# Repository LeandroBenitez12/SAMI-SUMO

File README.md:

# Robot Sumo Sami 🤖🏆

## Descripción del Proyecto

Este repositorio contiene el código y los recursos utilizados para el desarrollo de un robot Sumo llamado Sami.

El proyecto fue iniciado en 2022 por un grupo de estudiantes de Robótica del Industrial de Temperley, Buenos Aires, Argentina, entre ellos Leandro Benitez, Ezequiel Sierra, Abril Moyano y Facundo Timwki. Contamos con la invaluable colaboración de nuestro profesor, el Ingeniero Bustos Mariano.

Sami es un robot compacto y bien equilibrado diseñado específicamente para competir en las competencias de robótica, en particular en la Liga Nacional de Robótica (LNR) en Argentina. Durante el proceso de desarrollo, logramos el título de campeones en una competencia de robótica en el Instituto Técnico Nuestra Señora De Itatí, además avanzamos en cuanto a desarrollo personal y grupal, obtuvimos experiencia en la programación, diseño de PCB, 3D, el armado de robots, y fundiendo plomo, entre otras cosas...

## Características del Robot

- **Microcontrolador ESP32** para un rendimiento potente y una amplia capacidad de conectividad.
- **Pantalla OLED** para visualizar menús y estrategias en tiempo real.
- **Drivers Pololu 24v13** para el control preciso de motores y la maniobrabilidad del robot.
- **Sensores Sharp GP2Y0A60SZLF** para detectar obstáculos y oponentes.
- **Sensores de piso QRE1113 SMD y un LDR** utilizados en diversas estrategias de detección.
- Alimentación con **2 baterías LiPo en serie de 3 celdas**, logrando una tensión de 24V.
- Uso de un **convertidor Step-Down** para bajar la tensión y alimentar el microcontrolador.

## Estructura del Repositorio

- **/Software:** Contiene el código de programación en C++ para el robot Sami, basado en el entorno Arduino, y las librerías personalizadas.
- **/Hardware:** Incluye el diseño 3D del robot Sami, así como recursos relacionados con el armado físico y moldeado de plomo para alcanzar el límite de peso en la competencia.

## Instrucciones de Uso

1. Clona el repositorio en tu computadora local para acceder a todos los recursos y el código.
2. Explora el contenido de **/Software** para conocer la programación del robot y las diferentes estrategias disponibles.
3. Consulta el diseño 3D y la información en **/Hardware** para comprender la estructura y los componentes utilizados.

## Cómo Contribuir

¡Valoramos y agradecemos cualquier contribución que puedas brindar para mejorar nuestro robot Sami! Si deseas colaborar, sugerir mejoras o corregir problemas, sigue estos pasos:

1. Haz un fork de este repositorio y clona tu copia localmente.
2. Realiza los cambios y mejoras en tu rama, incluso si es para sugerir posibles soluciones o nuevas ideas.
3. Asegúrate de agregar o actualizar la documentación con tus contribuciones.
4. Realiza un pull request a nuestra rama principal para que podamos revisar y considerar tus aportes.

y videos....

https://github.com/LeandroBenitez12/SAMI_RBSUMO/assets/108737751/56b0725f-8328-4741-986b-e7431d0c3679

## Contacto

¡Nos encantaría recibir tus comentarios, sugerencias y cualquier tipo de feedback que nos ayude a mejorar nuestro proyecto Sami! Si deseas ponerte en contacto con nosotros, no dudes en escribirnos a:

- Leandro Benitez: leandrobenitezz2004@gmail.com
- Ezequiel Sierra: Sierraezequiel75@gmail.com

## Agradecimientos

Queremos expresar nuestro agradecimiento a todas las personas que nos han brindado apoyo y colaboración en este proyecto. ¡Sin su ayuda, no habríamos llegado tan lejos en el desarrollo de Sami y en nuestras competencias!

¡Estamos entusiasmados con los avances logrados hasta el momento y esperamos seguir mejorando y refinando nuestro robot Sumo Sami en el futuro! 🤖🏆

¡Gracias por tu interés en nuestro proyecto! Si necesitas más información o tienes otras preguntas, no dudes en hacérmelas. ¡Éxito en tus futuras competencias de robótica!

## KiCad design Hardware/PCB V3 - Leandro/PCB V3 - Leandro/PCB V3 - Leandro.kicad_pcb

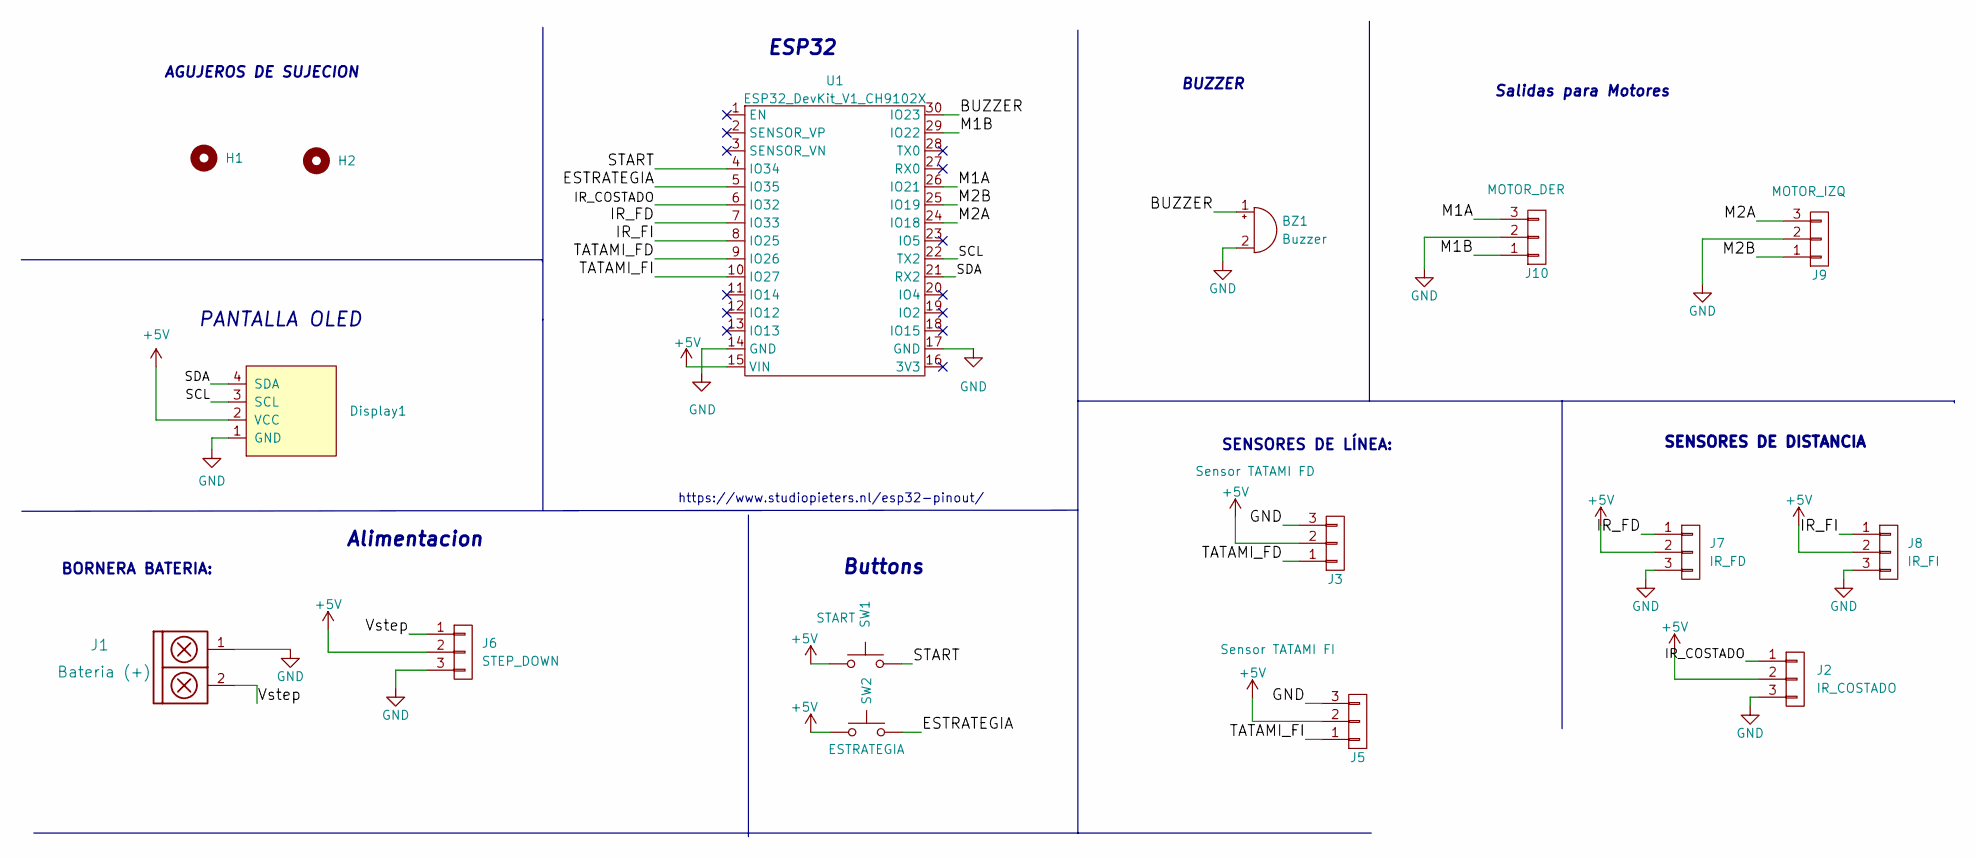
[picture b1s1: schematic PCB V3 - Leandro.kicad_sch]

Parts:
BZ1: Buzzer; Pin_strip_2
Display1: SSD1306-SSD1306-128x64_OLED; 128x64OLED
H1, H2: Mounting_Hole; pad_3mm
J1: Bateria (+); BORNERA2_AZUL
J2: IR_COSTADO; Pin_Strip_3
J3: Sensor TATAMI FD; Pin_Strip_3
J5: Sensor TATAMI FI; Pin_Strip_3
J6: STEP_DOWN; Pin_Strip_3
J7: IR_FD; Pin_Strip_3
J8: IR_FI; Pin_Strip_3
J9: MOTOR_IZQ; Pin_Strip_3
J10: MOTOR_DER; Pin_Strip_3
SW1: START; Pin_Header_2
SW2: ESTRATEGIA; Pin_Header_2
U1: ESP32_DevKit_V1_CH9102X

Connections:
+5V: Display1.2 (VCC), J2.2, J3.2, J5.2, J6.2, J7.2, J8.2, SW1.1, SW2.1, U1.15 (VIN)
/BUZZER: BZ1.1 (-), U1.30 (IO23)
/ESTRATEGIA: SW2.2, U1.5 (IO35)
/IR_COSTADO: J2.1, U1.6 (IO32)
/IR_FD: J7.1, U1.7 (IO33)
/IR_FI: J8.1, U1.8 (IO25)
/M1A: J10.3, U1.26 (IO21)
/M1B: J10.1, U1.29 (IO22)
/M2A: J9.3, U1.24 (IO18)
/M2B: J9.1, U1.25 (IO19)
/SCL: Display1.3 (SCL), U1.22 (TX2)
/SDA: Display1.4 (SDA), U1.21 (RX2)
/START: SW1.2, U1.4 (IO34)
/TATAMI_FD: J3.1, U1.9 (IO26)
/TATAMI_FI: J5.1, U1.10 (IO27)
/Vstep: J1.2, J6.1
GND: BZ1.2 (+), Display1.1 (GND), J1.1, J2.3, J3.3, J5.3, J6.3, J7.3, J8.3, J9.2, J10.2, U1.14 (GND), U1.17 (GND)

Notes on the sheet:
SENSORES DE LÍNEA:
Buttons
ESP32
BORNERA BATERIA:
https://www.studiopieters.nl/esp32-pinout/
PANTALLA OLED
Alimentacion
SENSORES DE DISTANCIA
AGUJEROS DE SUJECION
Salidas para Motores
BUZZER

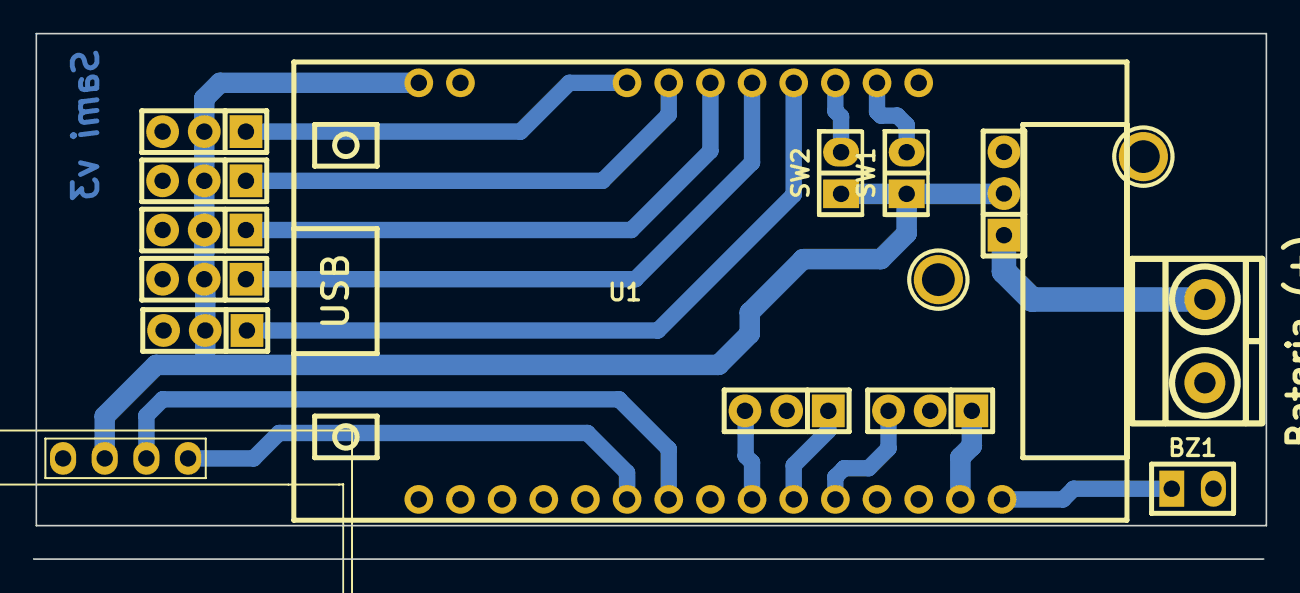
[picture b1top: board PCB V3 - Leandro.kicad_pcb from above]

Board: 2 copper layers, 75.2 x 32.0 mm, 16 parts (0 on the bottom side), 17 nets.

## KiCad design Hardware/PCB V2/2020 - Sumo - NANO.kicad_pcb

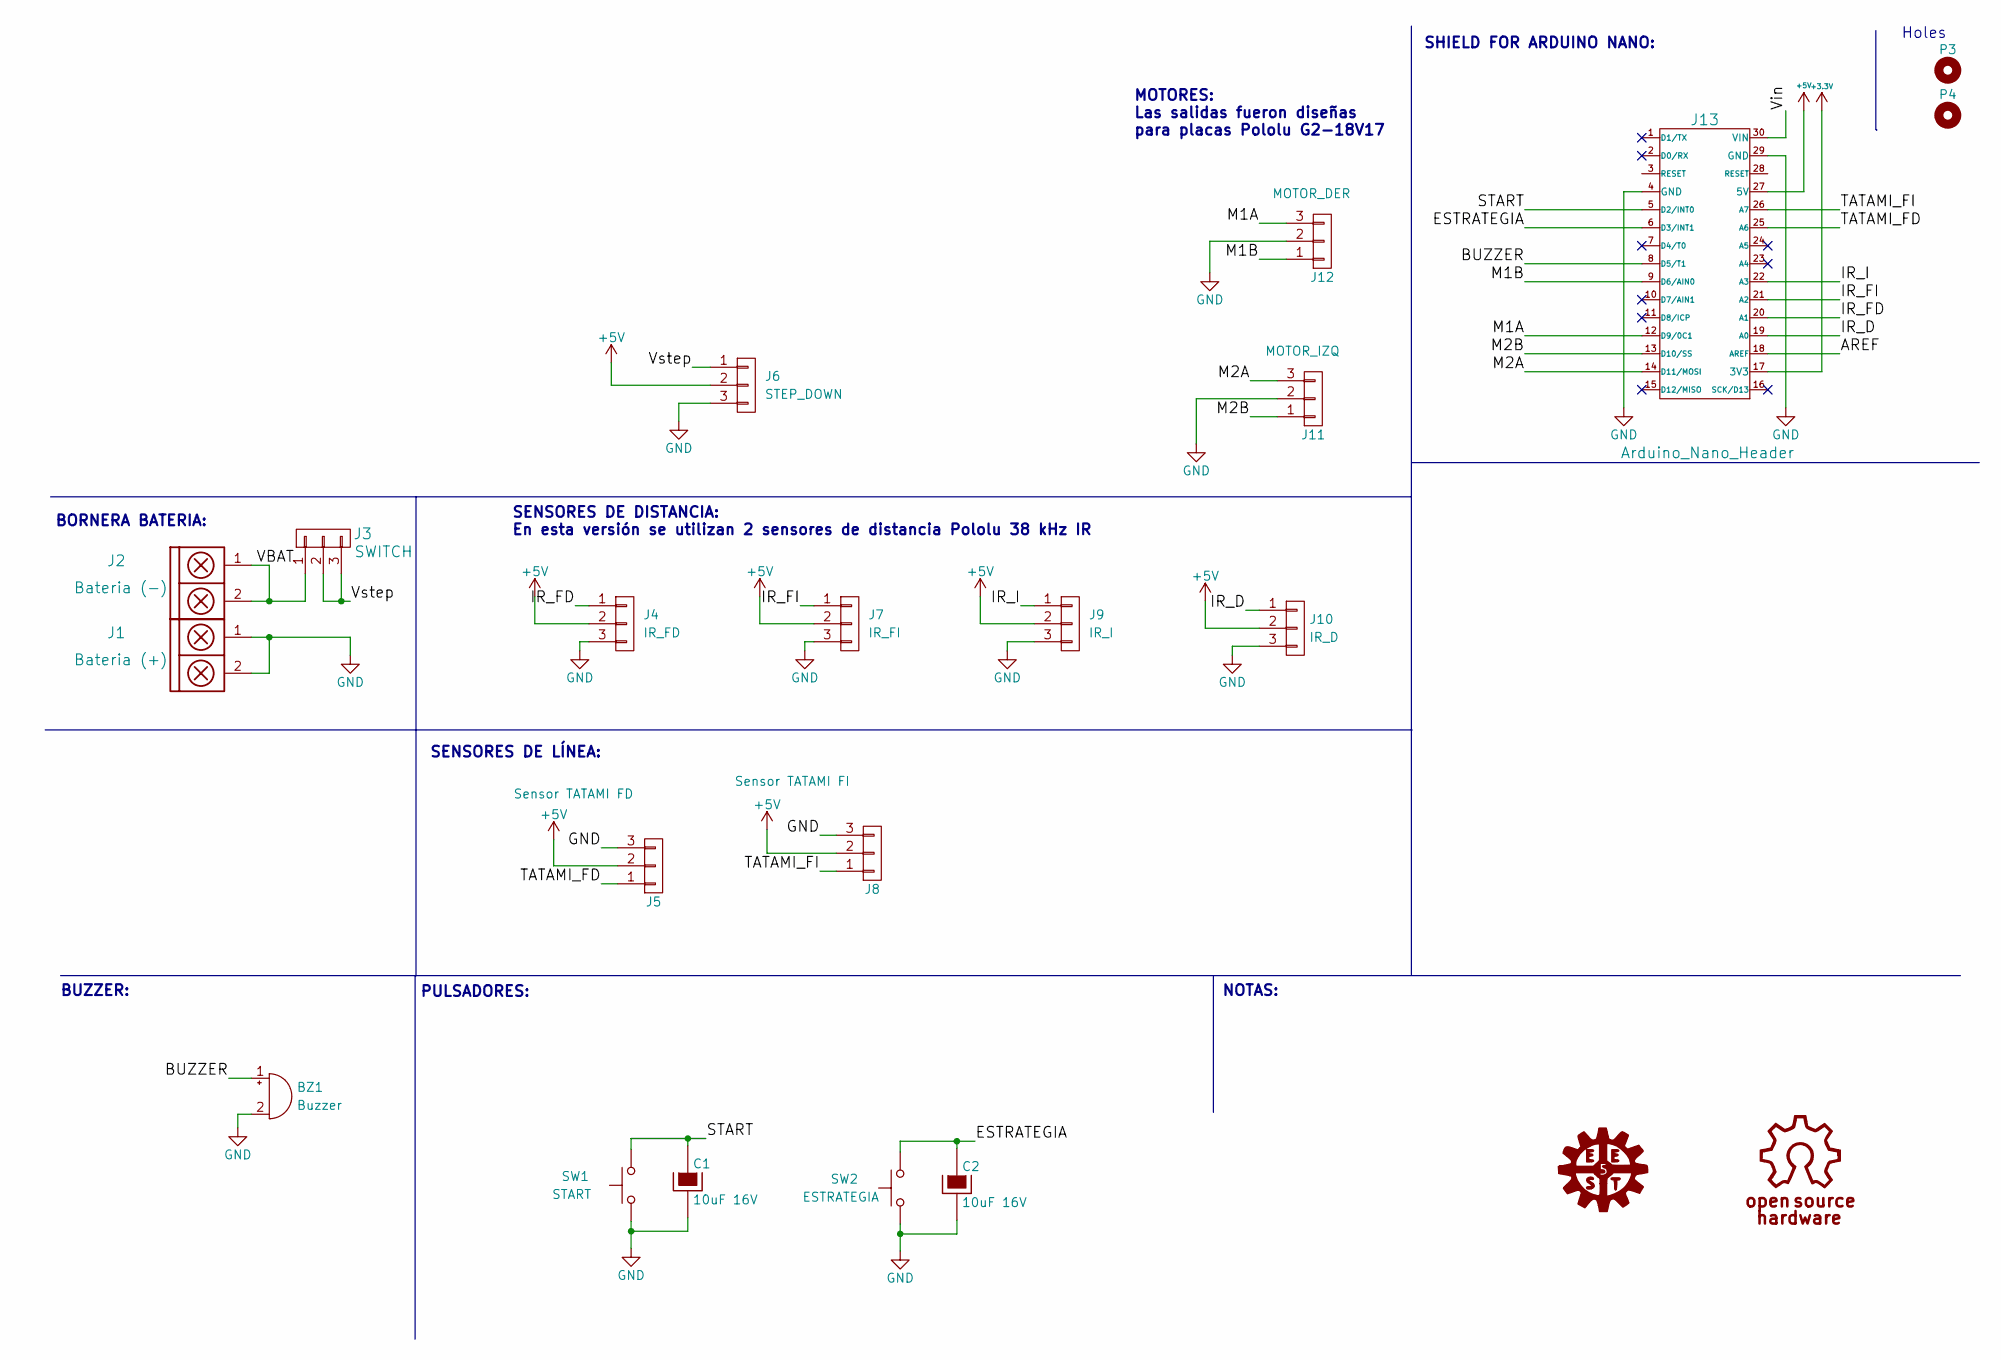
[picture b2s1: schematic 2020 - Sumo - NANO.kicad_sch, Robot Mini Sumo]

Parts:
BZ1: Buzzer; Pin_strip_2
C1, C2: 10uF 16V; CAP_TAN_A
J1: Bateria (+); BORNERA2_AZUL
J2: Bateria (-); BORNERA2_AZUL
J3: SWITCH; SW_SPDT_TH_Vertical
J4: IR_FD; Pin_Strip_3
J5: Sensor TATAMI FD; Pin_Strip_3
J6: STEP_DOWN; Pin_Strip_3
J7: IR_FI; Pin_Strip_3
J8: Sensor TATAMI FI; Pin_Strip_3
J9: IR_I; Pin_Strip_3
J10: IR_D; Pin_Strip_3
J11: MOTOR_IZQ; Pin_Strip_3
J12: MOTOR_DER; Pin_Strip_3
J13: Arduino_Nano_Header; arduino_nano_header
P3, P4: Mounting_Hole; Separador_M3_5mm
SW1: START; Pin_Header_2
SW2: ESTRATEGIA; Pin_Header_2

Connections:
+3V3: J13.17 (3V3)
+5V: J4.2, J5.2, J6.2, J7.2, J8.2, J9.2, J10.2, J13.27 (5V)
/AREF: J13.18 (AREF)
/BUZZER: BZ1.1 (-), J13.8 (D5/T1)
/ESTRATEGIA: C2.1, J13.6 (D3/INT1), SW2.2
/IR_D: J10.1, J13.19 (A0)
/IR_FD: J4.1, J13.20 (A1)
/IR_FI: J7.1, J13.21 (A2)
/IR_I: J9.1, J13.22 (A3)
/M1A: J12.3, J13.12 (D9/0C1)
/M1B: J12.1, J13.9 (D6/AIN0)
/M2A: J11.3, J13.14 (D11/MOSI)
/M2B: J11.1, J13.13 (D10/SS)
/START: C1.1, J13.5 (D2/INT0), SW1.2
/TATAMI_FD: J5.1, J13.25 (A6)
/TATAMI_FI: J8.1, J13.26 (A7)
/VBAT: J2.1, J2.2, J3.1
/Vin: J13.30 (VIN)
/Vstep: J3.2, J3.3, J6.1
GND: BZ1.2 (+), C1.2, C2.2, J1.1, J1.2, J4.3, J5.3, J6.3, J7.3, J8.3, J9.3, J10.3, J11.2, J12.2, J13.4 (GND), J13.29 (GND), SW1.1, SW2.1

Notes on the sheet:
SENSORES DE LÍNEA:
MOTORES: Las salidas fueron diseñas para placas Pololu G2-18V17
Holes
BORNERA BATERIA:
NOTAS:
BUZZER:
SHIELD FOR ARDUINO NANO:
SENSORES DE DISTANCIA: En esta versión se utilizan 2 sensores de distancia Pololu 38 kHz IR
PULSADORES:

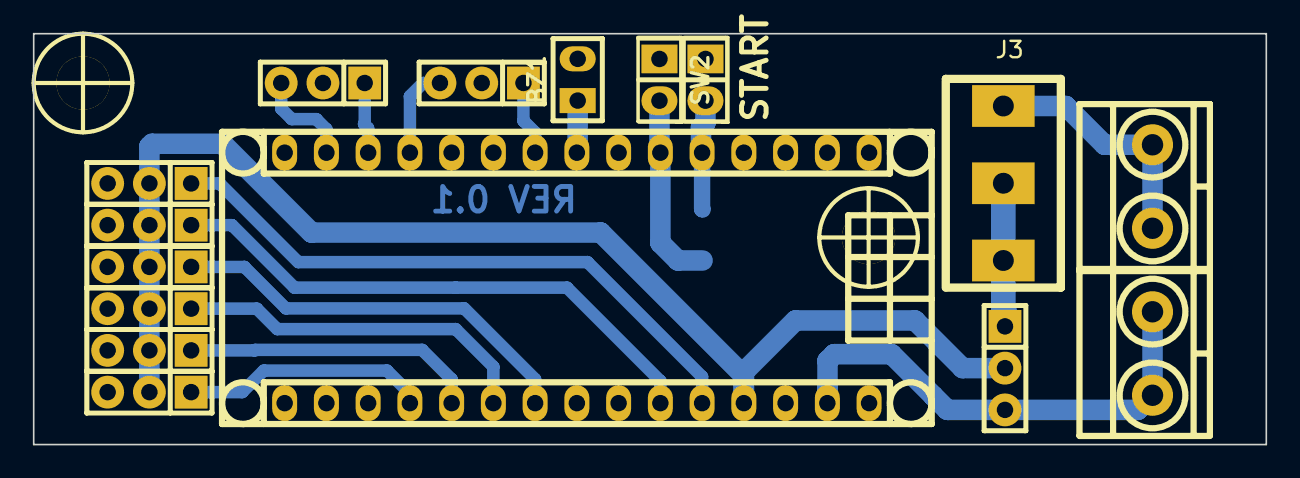
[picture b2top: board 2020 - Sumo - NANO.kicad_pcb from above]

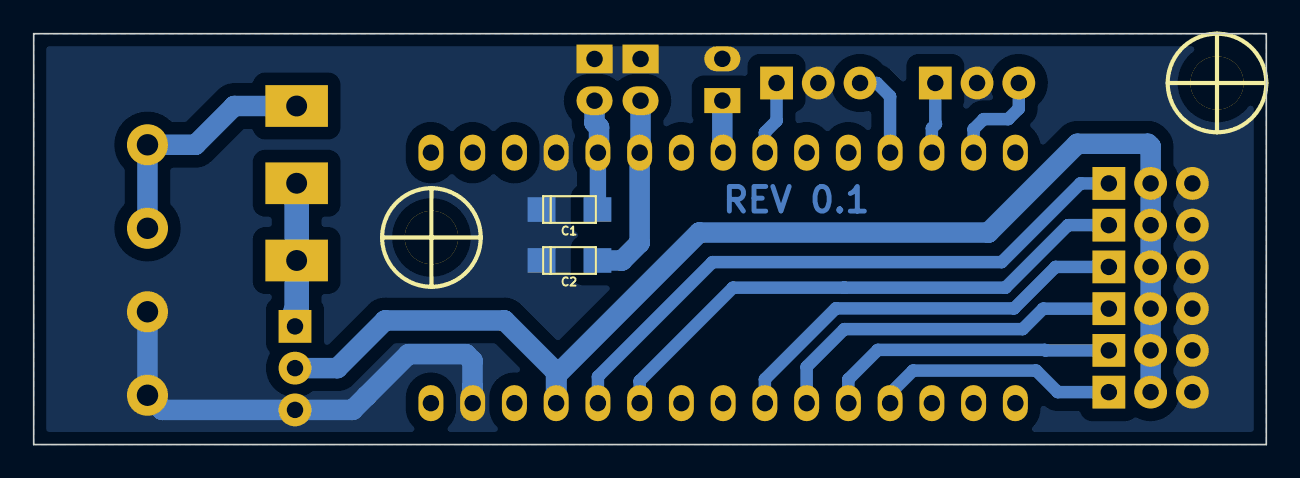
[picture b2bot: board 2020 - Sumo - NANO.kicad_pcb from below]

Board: 2 copper layers, 75.0 x 25.0 mm, 20 parts (2 on the bottom side), 17 nets.

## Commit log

2022-08-27 Add the folders
2022-08-27 el robot ahora detecta sensores de piso y gira
2022-08-27 Realice POO de motores
2022-08-27 Realice el POO de sensores anda bien
2022-08-27 Correciones sugeridas por angel y agregue class button y buzzer
2022-08-27 Realice la maquina de estados pero tengo problemas
2022-08-27 Ahora anda gracias f0n
2022-08-29 codigo inicial echo por Lenadro
2022-08-29 maquina de estados y todos los chiches
2022-09-01 contine switch
2022-09-02 codigo base terminado (falta probar)
2022-09-03 agregue la prueba de sensores tatami
2022-09-03 hice test de tatami
2022-09-03 pruebas
2022-09-03 El robot lo probamos y anda, no andan los sensores tatami pero creemos que por hardware
2022-09-03 probando como detecta el sensor
2022-09-03 ahora si andan los sensores y todo :)
2022-09-09 este anda todo digamos
2022-09-09 cambios para probar los dos sharp
2022-09-10 abda joya
2022-09-10 falta strategy nomas
2022-09-24 Pase las clases a librerias y termine la primera estrategia
2022-09-24 pase las clases a librerias y termine la estrategia 1 del codigo
2022-09-24 elimine archivos innecesarios
2022-09-26 agregue los codigos para probar cada sensor
2022-09-26 correccion de errores
2022-10-03 Estuve realizando los test de sensores y estan okey
2022-10-04 sUMO SAMIMOTORES POO ANDA JOYA
2022-10-05 Hice pruebas pero el codigo que hizo eze no anda nada bien
2022-10-05 cambie bastante
2022-10-07 Pruebas de Sami con exitos
2022-10-08 cambios para llevar a UTN
2022-10-10 probando post competencia UTN falla de boton y no posee strategy
2022-10-11 haciendo placa nueva de sami con esp32
2022-10-12 termine la placa hay que ver que dice bustos
2022-10-12 corregi algo quevi de gnd
2022-10-12 falta la correccion de Bustos y diseñar el svg
2022-10-12 falta los svg y que me corrija bustos
2022-10-13 placa para fabricar ya
2022-10-13 placa lista con 3d
2022-10-14 Realizando pruebas con el button , hace ruido todasvia
2022-10-14 ahora andan los putos botones
2022-10-15 Ordenando pines respecto del esp32
2022-10-16 REGULANDO LIBRERIA DE SENSOR SHARP
2022-10-16 actualizando pines de ESP32
2022-10-16 corrigiendo cosas que me dijo bustos
2022-10-17 empece el codigo definitivo de Sami con varias estrategias
2022-10-17 codigo por mi parte listo falta probar motoresw pero en mi pc no compilaaaa
2022-10-17 ordene todo mejor y modifique una variable de las librerias para declararla dentro de la clase
2022-10-17 separe la estrategias en codigos aparte para probar una por una
2022-10-18 agregue el menu del display oled para acceder a cada estrategia
2022-10-18 Probe A Sami asi nomas y no me andan BIEN Los sensores lpm el resto joya
2022-10-18 cambios de sch
2022-10-26 agregue la clase de controlador de motores y demas mejores sugeridas por fon
2022-10-26 Cambios realizados para competir en La Salle
2022-10-26 usada en lasalle
2022-10-31 arreglos en la prueba de cada estrategia
2022-11-01 codigo funcional y probado con los giros de reposicionamiento
2022-11-01 pruebas realizadas antes de ITATI
2022-11-02 3 estrategias perfectamente funcionales
2022-11-02 ganamos en ITATI CON ESTOOOOOO DALE SAMI GUACHO
2022-11-05 agregue la estrategia agresiva
2022-11-08 agregue un codigo nuevo con una nueva estrategia a probar
2022-11-08 areglo de un par de errores de sintanxis
2022-11-11 cambios en el codigo
2022-11-11 empece con el codigo de Ryo
2022-11-15 CAMBIOS PARA UNA NUEVA STRATEGY RONALDINHO
2022-11-23 codigo de Ryo usado en antes de la final nacional en las pruebas del dia anterior
